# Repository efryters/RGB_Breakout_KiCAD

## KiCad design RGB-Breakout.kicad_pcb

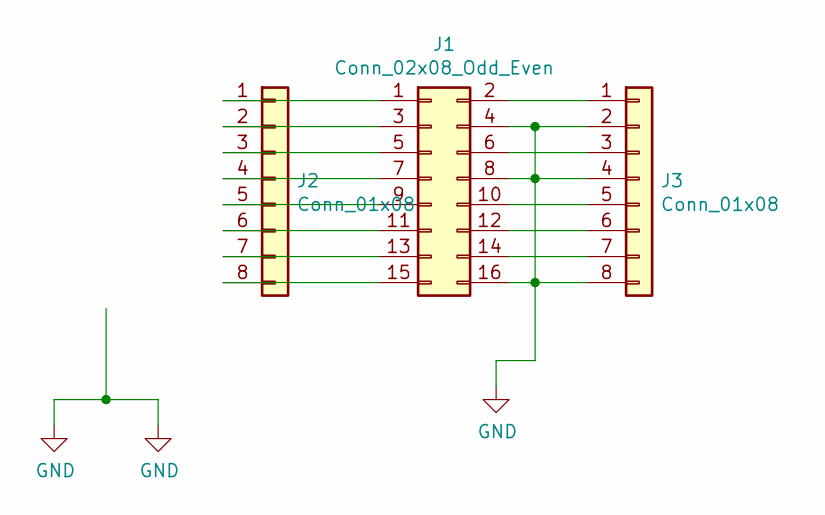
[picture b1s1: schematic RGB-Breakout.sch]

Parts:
J1: Conn_02x08_Odd_Even; IDC-Header_2x08_P2.54mm_Vertical
J2, J3: Conn_01x08; PinSocket_1x08_P2.54mm_Vertical

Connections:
GND: J1.4, J1.8, J1.16, J3.2, J3.4, J3.8
unnamed: J1.1, J2.1
unnamed: J1.2, J3.1
unnamed: J1.3, J2.2
unnamed: J1.5, J2.3
unnamed: J1.6, J3.3
unnamed: J1.7, J2.4
unnamed: J1.9, J2.5
unnamed: J1.10, J3.5
unnamed: J1.11, J2.6
unnamed: J1.12, J3.6
unnamed: J1.13, J2.7
unnamed: J1.14, J3.7
unnamed: J1.15, J2.8

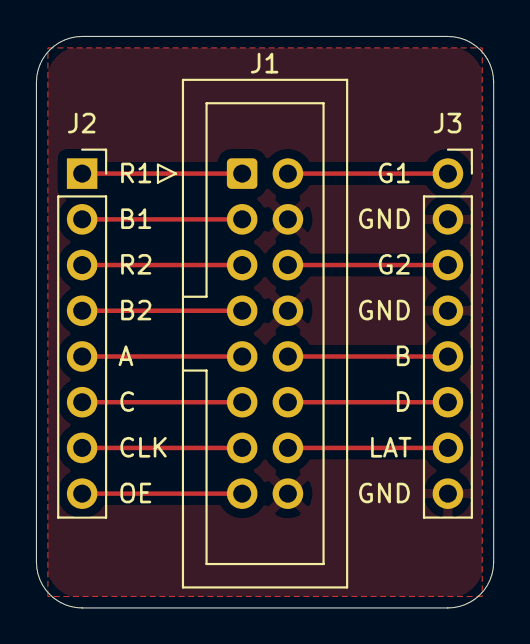
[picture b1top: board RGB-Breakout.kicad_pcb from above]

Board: 2 copper layers, 25.4 x 31.8 mm, 3 parts (0 on the bottom side), 14 nets.
